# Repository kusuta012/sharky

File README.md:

# SHARKY 

DISCLAIMER: This project is for educational and security research purposes only. The user is solely responsible for compliance with local laws regarding radio interference, and the author assumes no liability for any misuse or legal consequences arising from this hardware.

This project is the most hacky vibes kinda I saw this in my youtube recommendation, its a 2.4ghz wifi and bluetooth jammer/deauther. It uses a esp32 and two nRF24L01+PA+LNA which makes it crazy at max power.

# NOTE !!! 🟥🟥🟥

**For the 2nd reviewer pls note since the lipo battery is out of stock from the website , and i couldn't find anywhere else online , I am going to buy it locally , so it might differ with the requested funding ammount pls ping on slack for any confusion**

# FLASHING INSTRUCTIONS

- You need to cloen this repo, open the folder in the IDE.
- PlatformIO will automatically detect the platformio.ini and download the RF24 library.
- Connect your ESP32 and click the upload button in the bottom status bar.
- After you are good to go, it will start working!!

# SHOWCASE

# PCB 

# SEEEDSTUDIO CART 

# QUARTZCOMPONENTS CART 

# BOM 

| Name | Qty | Price (INR) | Vendor | Link |
|------|-----|--------------|--------|------|
| TP4056 Module | 1 | 16 | QuartzComponents | [Link](https://quartzcomponents.com/products/tp4056-battery-charging-protection-module-type-c) |
| NRF24L01+PA+LNA | 2 | 276 | QuartzComponents | [Link](https://quartzcomponents.com/products/nrf24l01-pa-lna-wireless-2-4ghz-rf-transceiver-module-with-sma-antenna) |
| ESP32-DEVKITV1 | 1 | 345 | QuartzComponents | [Link](https://quartzcomponents.com/products/esp32-30-pin-development-board-with-wi-fi-and-bluetooth) |
| JST-XH 2.54mm 2P Connector | 1 | 3 | QuartzComponents | [Link](https://quartzcomponents.com/products/2-pin-jst-male-2-54-pitch) |
| 100uF Electrolytic Capacitor | 2 | 6 | QuartzComponents | [Link](https://quartzcomponents.com/products/100uf-25v-radial-electrolytic-capacitor) |
| SPDT Slide Switch | 1 | 6 | QuartzComponents | [Link](https://quartzcomponents.com/products/dpdt-miniature-slide-switch) |
| 3.7V 1200mAh Li-Po Battery | 1 | 228 | Local Shop | Local Shop |
| M3 6mm Screw | 1 | 5 | QuartzComponents | [Link](https://quartzcomponents.com/products/phillips-head-m3-6mm-bolt-mounting-screw-for-pcb) |
| M3 12mm Screw | 1 | 8 | QuartzComponents | [Link](https://quartzcomponents.com/collections/all/products/phillips-head-m3-12mm-bolt-mounting-screw-for-pcb-pack-of-4) |

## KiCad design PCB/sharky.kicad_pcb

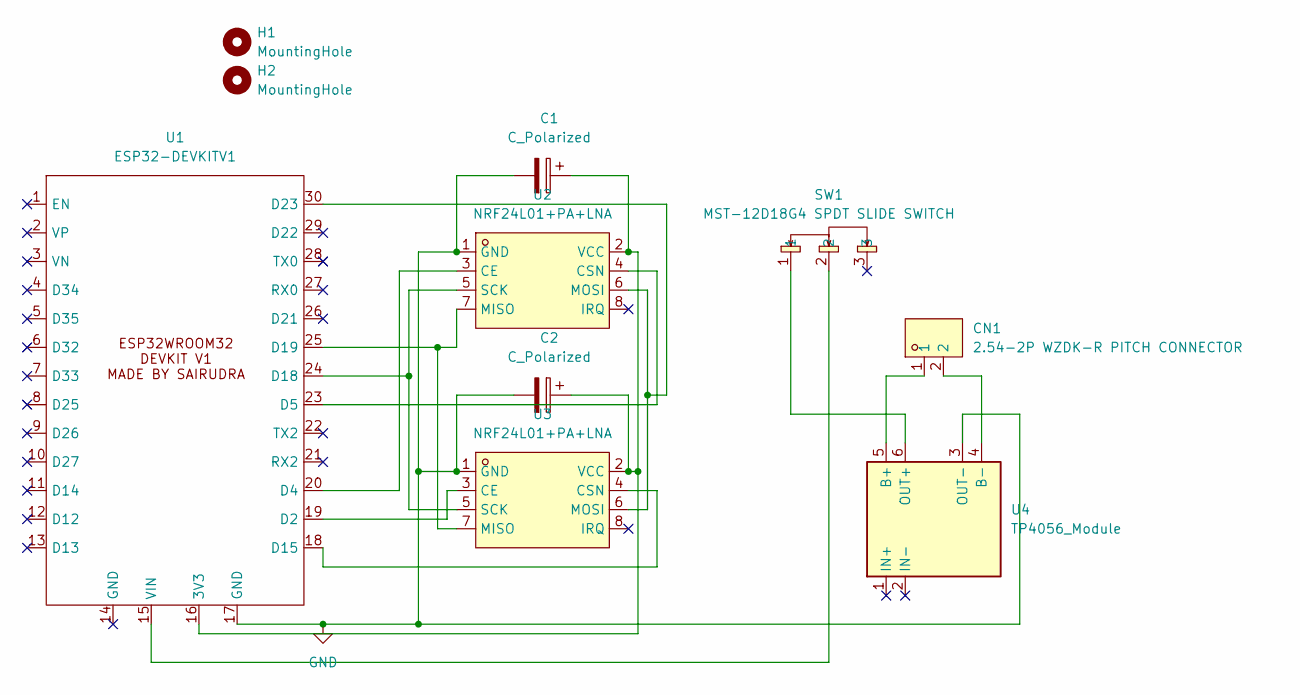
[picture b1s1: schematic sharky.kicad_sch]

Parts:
C1, C2: C_Polarized; CP_Radial_D6.3mm_P2.50mm
CN1: 2.54-2P WZDK-R PITCH CONNECTOR; CONN-TH_2.54-2P-WZDK-R-PITCH-CONNECTOR; LCSC Part C49023803
H1, H2: MountingHole; MountingHole_3.2mm_M3_Pad
SW1: MST-12D18G4 SPDT SLIDE SWITCH; SW-SMD_MST-12D18G4-SPDT-SLIDE-SWITCH; LCSC Part C49023767
U1: ESP32-DEVKITV1; ESP32DEVIKITV1
U2, U3: NRF24L01+PA+LNA; COMM-TH_L41.0-W15.5-P2.54_NRF24L01; LCSC Part C9900187674
U4: TP4056_Module; TP4056-18650

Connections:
GND: C1.2, C2.2, U1.17 (GND), U2.1 (GND), U3.1 (GND), U4.3 (OUT-)
unnamed: C1.1, C2.1, U1.16 (3V3), U2.2 (VCC), U3.2 (VCC)
unnamed: U1.19 (D2), U3.3 (CE)
unnamed: U1.20 (D4), U2.3 (CE)
unnamed: U1.23 (D5), U2.4 (CSN)
unnamed: U1.18 (D15), U3.4 (CSN)
unnamed: U1.24 (D18), U2.5 (SCK), U3.5 (SCK)
unnamed: U1.25 (D19), U2.7 (MISO), U3.7 (MISO)
unnamed: U1.30 (D23), U2.6 (MOSI), U3.6 (MOSI)
unnamed: SW1.2, U1.15 (VIN)
unnamed: CN1.1, U4.5 (B+)
unnamed: CN1.2, U4.4 (B-)
unnamed: SW1.1, U4.6 (OUT+)

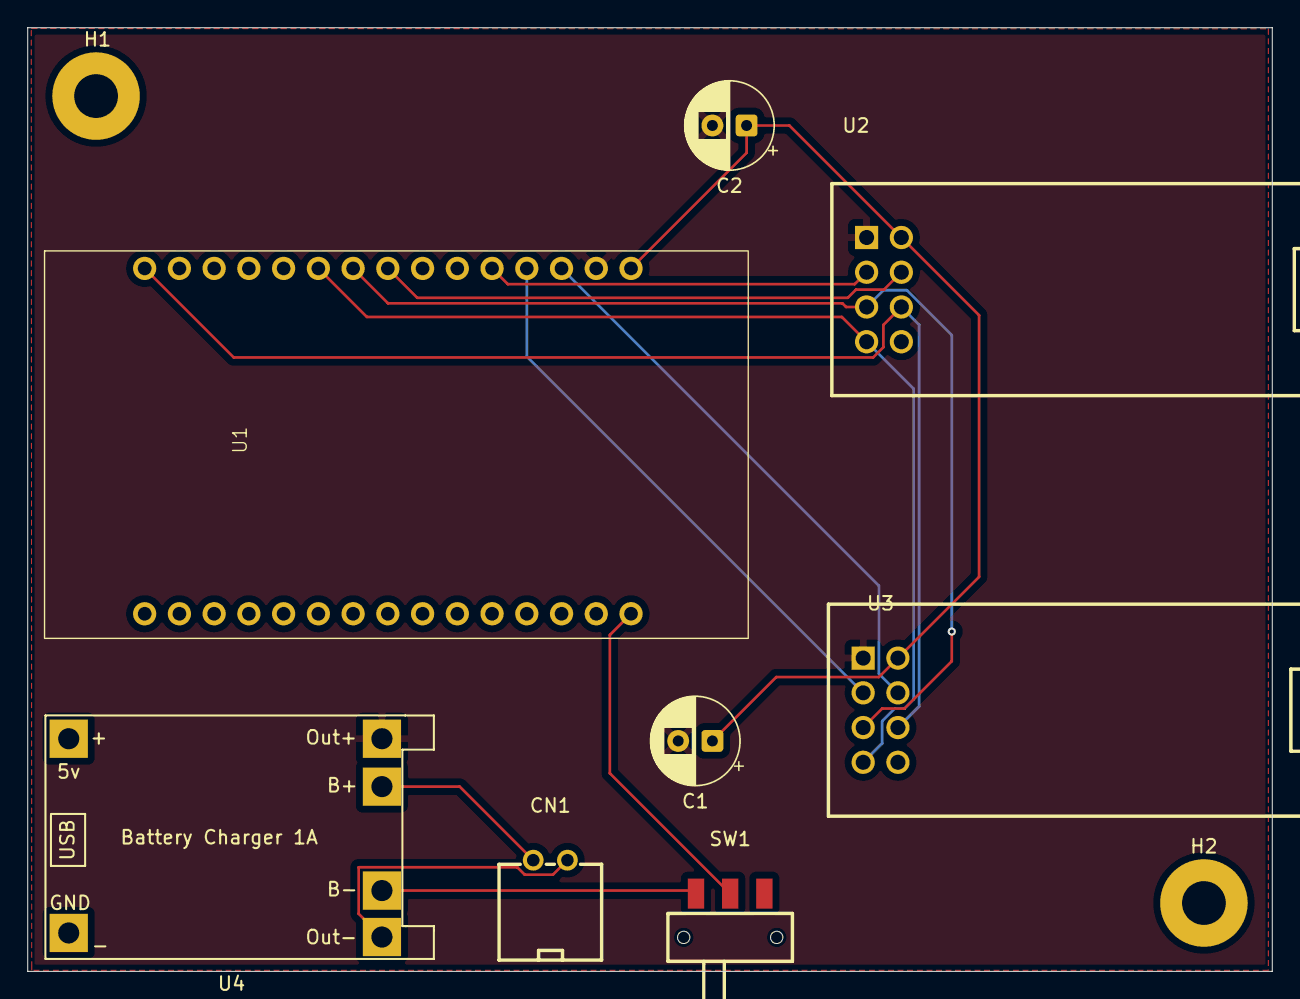
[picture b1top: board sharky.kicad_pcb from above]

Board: 2 copper layers, 91.0 x 69.0 mm, 10 parts (0 on the bottom side), 13 nets.

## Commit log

2026-01-24 Intial Commit
2026-01-24 added the links
2026-01-24 add M3 screws
2026-01-24 Update README with project overview and BOM
    Added project details, components list, and images.
2026-01-25 Update BOM
2026-01-25 Updated cad
2026-01-25 Update prices for NRF24L01+PA+LNA and capacitor
2026-01-25 Adjust prices in bom.csv
    Updated prices for NRF24L01+PA+LNA and 100uF Electrolytic Capacitor.
2026-01-25 Update supplier name for SPDT Slide Switch
2026-02-03 Update README.md with additional images
    Added new images to the PCB and QUARTZCOMPONENTS CART sections.
2026-02-12 Add missing build files and flashing instructions per reviewer feedback
2026-02-27 Update supplier information for Li-Po battery
2026-02-27 Update README with battery sourcing note
    Added note about battery sourcing for reviewers.
